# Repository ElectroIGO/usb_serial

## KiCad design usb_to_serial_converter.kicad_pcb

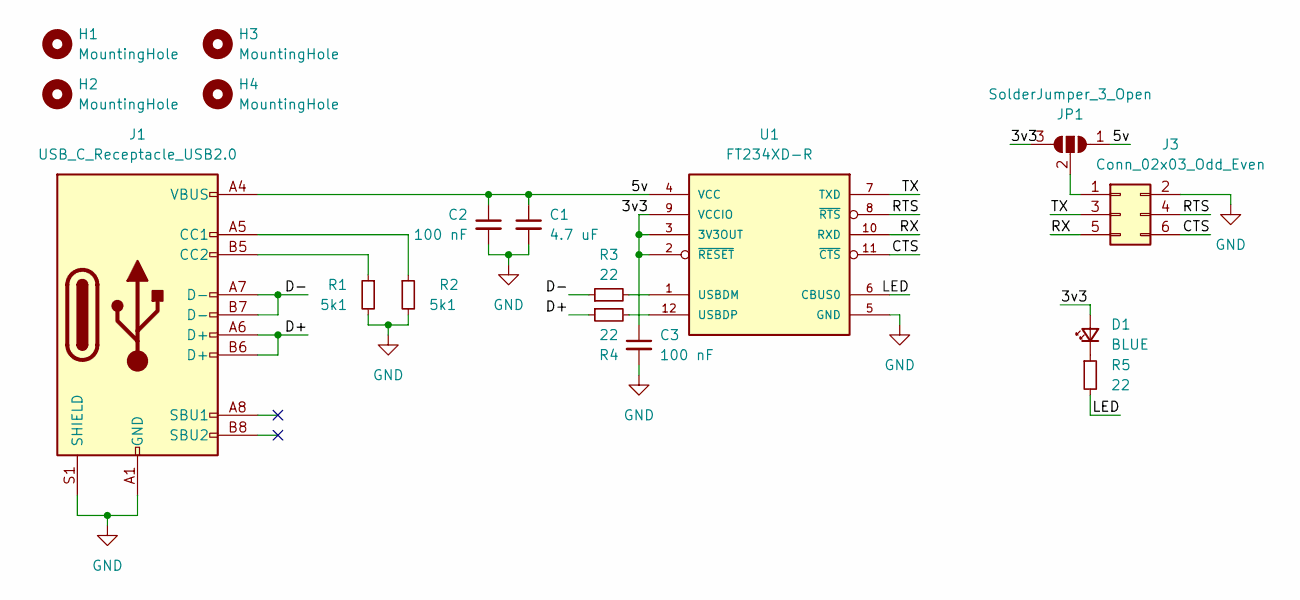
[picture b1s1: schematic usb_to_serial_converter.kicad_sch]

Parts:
C1: 4.7 uF; C_0805_2012Metric
C2, C3: 100 nF; C_0603_1608Metric
D1: BLUE; D_0603_1608Metric
H1, H2, H3, H4: MountingHole; MountingHole_3.2mm_M3
J1: USB_C_Receptacle_USB2.0; USB_C_Receptacle_HRO_TYPE-C-31-M-12
J3: Conn_02x03_Odd_Even; PinSocket_2x03_P2.54mm_Vertical_SMD
JP1: SolderJumper_3_Open; SolderJumper-3_P1.3mm_Open_RoundedPad1.0x1.5mm_NumberLabels
R1, R2: 5k1; R_0603_1608Metric
R3, R4, R5: 22; R_0603_1608Metric
U1: FT234XD-R; SON45P300X300X80-13N; PARTREV Version 1.2

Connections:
/3v3: C3.1, D1.2 (A), JP1.3 (B), U1.2 (~RESET), U1.3 (3V3OUT), U1.9 (VCCIO)
/5v: C1.1, C2.1, J1.A4 (VBUS), J1.A9 (VBUS), J1.B4 (VBUS), J1.B9 (VBUS), JP1.1 (A), U1.4 (VCC)
/CTS: J3.6, U1.11 (~CTS)
/D+: J1.A6 (D+), J1.B6 (D+), R4.1
/D-: J1.A7 (D-), J1.B7 (D-), R3.1
/LED: R5.2, U1.6 (CBUS0)
/RTS: J3.4, U1.8 (~RTS)
/RX: J3.5, U1.10 (RXD)
/TX: J3.3, U1.7 (TXD)
GND: C1.2, C2.2, C3.2, J1.A1 (GND), J1.A12 (GND), J1.B1 (GND), J1.B12 (GND), J1.S1 (SHIELD), J3.2, R1.2, R2.2, U1.5 (GND), U1.13 (GND)
unnamed: D1.1 (K), R5.1
unnamed: J1.A5 (CC1), R2.1
unnamed: J1.B5 (CC2), R1.1
unnamed: J3.1, JP1.2 (C)
unnamed: R3.2, U1.1 (USBDM)
unnamed: R4.2, U1.12 (USBDP)

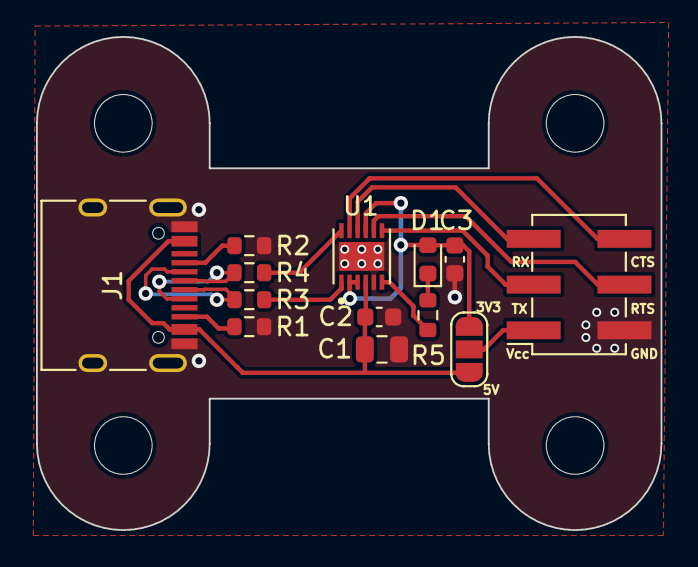
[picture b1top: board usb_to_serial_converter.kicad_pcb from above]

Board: 2 copper layers, 34.7 x 27.4 mm, 17 parts (0 on the bottom side), 16 nets.

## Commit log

2023-07-02 0.1v
    USB-C to serial interface (UART).
